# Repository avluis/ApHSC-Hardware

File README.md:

# ApHSC - Hardware
# Eagle CAD files for the ApHSC
  By: [Luis E Alvarado](mailto:admin@avnet.ws)
  
  [Software](https://github.com/avluis/ApHSC) | 
  [Hardware](https://github.com/avluis/ApHSC-Hardware)
  
# Purpose:
	To drive a ComfortHeat "Automotive Carbon Fiber Seat Heaters"
  	by Rostra with the stock control panel of a vehicle, in my case, a 2011 Suzuki Kizashi
  [Rostra Kit: 250-1872 - Universal Kit, Double thumb-dial Switch](http://www.rostra.com/manuals/250-1870_Form5261.pdf)

# Screenshots:

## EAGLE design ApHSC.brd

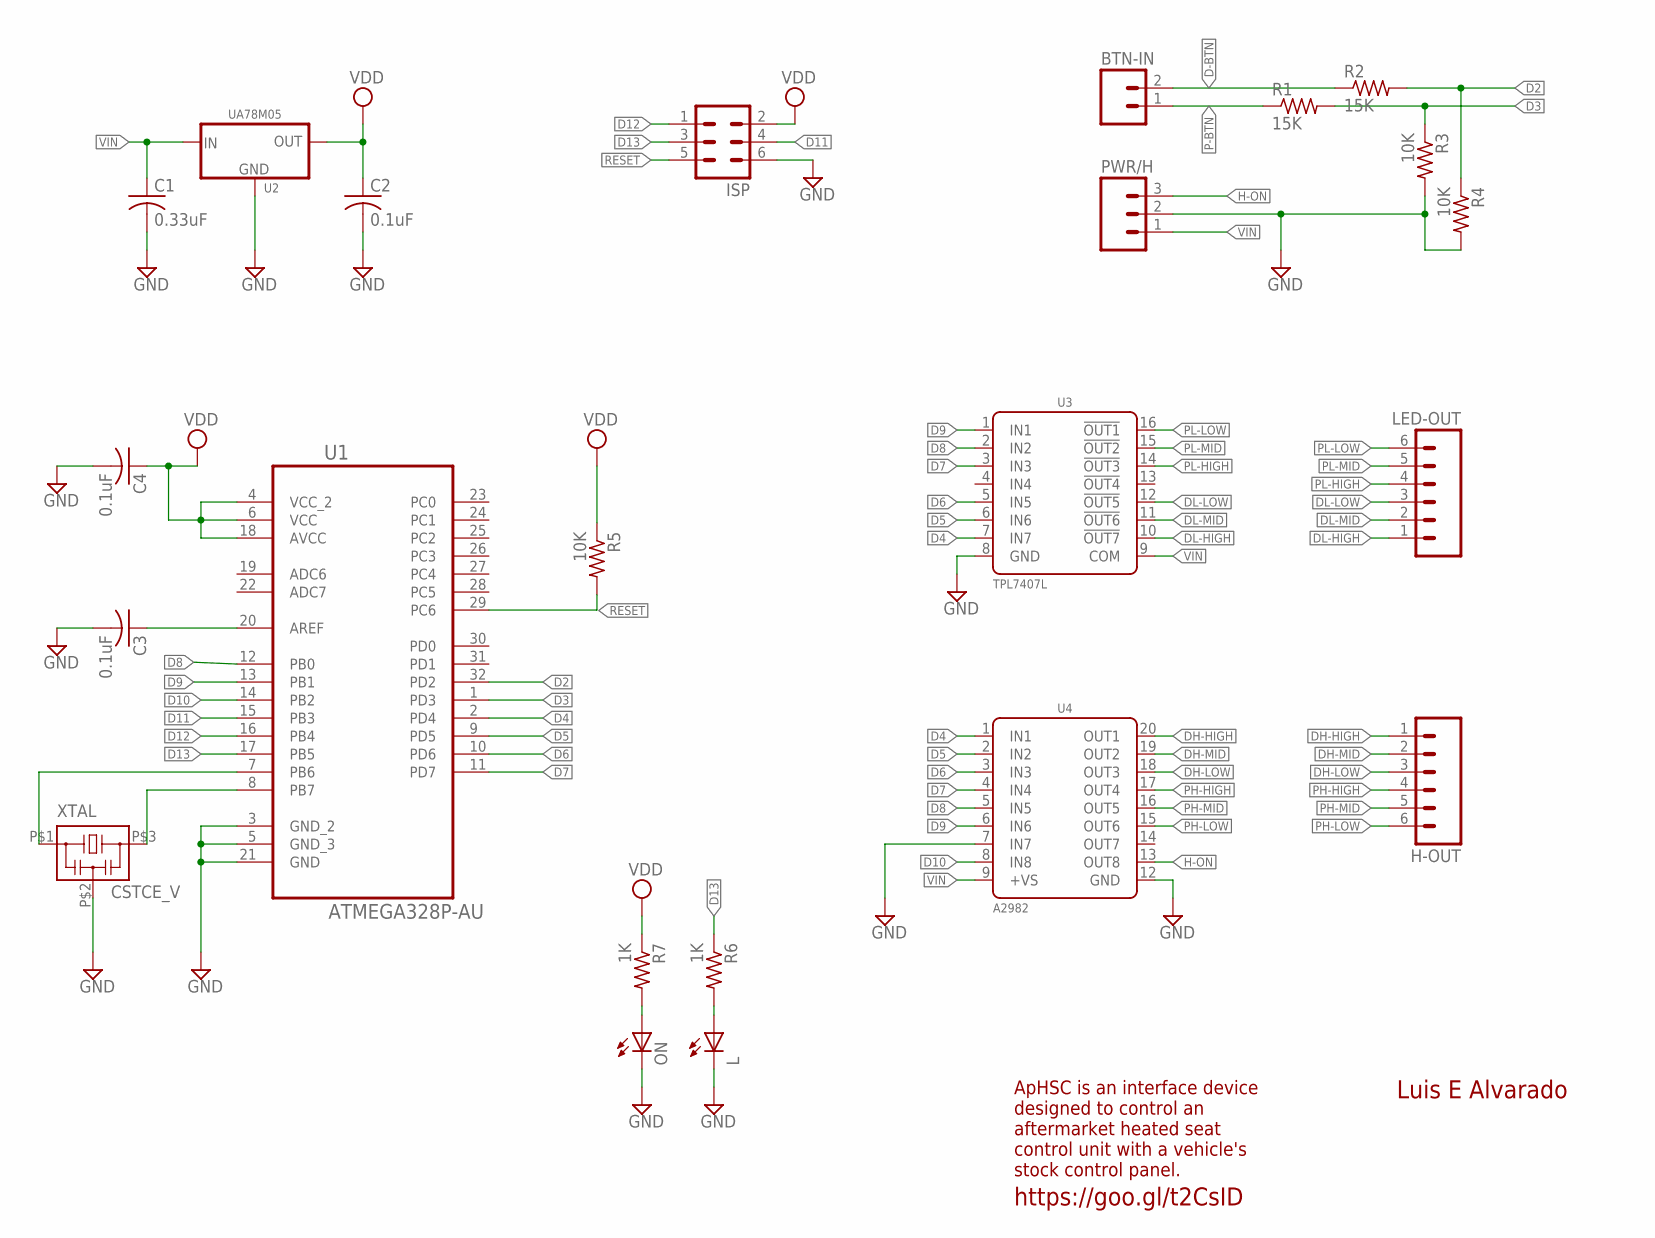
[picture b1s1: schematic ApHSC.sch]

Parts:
BTN-IN: M02PTH; 1X02
C1: 0.33uF; C0603
C2, C3, C4: 0.1uF; C0603
H-OUT: M06SIP; 1X06
ISP: MA03-2
L: LEDCHIP-LED0603; CHIP-LED0603
LED-OUT: M06SIP; 1X06
ON: LEDCHIP-LED0603; CHIP-LED0603
PWR/H: M03PTH; 1X03
R1, R2: 15K; R0603
R3, R4, R5: 10K; R0603
R6, R7: 1K; R0603
U1: ATMEGA328P-AU; QFP80P900X900X120-32N
U2: UA78M05; SOT223
U3: TPL7407L; SOIC16N
U4: A2982; SOIC20W
XTAL: CSTCE_V

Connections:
AREF: C3.1, U1.20 (AREF)
D2: R2.2, R4.1, U1.32 (PD2)
D3: R1.2, R3.1, U1.1 (PD3)
D4: U1.2 (PD4), U3.7 (IN7), U4.1 (IN1)
D5: U1.9 (PD5), U3.6 (IN6), U4.2 (IN2)
D6: U1.10 (PD6), U3.5 (IN5), U4.3 (IN3)
D7: U1.11 (PD7), U3.3 (IN3), U4.4 (IN4)
D8: U1.12 (PB0), U3.2 (IN2), U4.5 (IN5)
D9: U1.13 (PB1), U3.1 (IN1), U4.6 (IN6)
D10: U1.14 (PB2), U4.8 (IN8)
D11: ISP.4, U1.15 (PB3)
D12: ISP.1, U1.16 (PB4)
D13: ISP.3, R6.1, U1.17 (PB5)
D-BTN: BTN-IN.2, R2.1
DH-HIGH: H-OUT.1, U4.20 (OUT1)
DH-LOW: H-OUT.3, U4.18 (OUT3)
DH-MID: H-OUT.2, U4.19 (OUT2)
DL-HIGH: LED-OUT.1, U3.10 (!OUT7)
DL-LOW: LED-OUT.3, U3.12 (!OUT5)
DL-MID: LED-OUT.2, U3.11 (!OUT6)
GND: C1.2, C2.2, C3.2, C4.2, ISP.6, L.C, ON.C, PWR/H.2, R3.2, R4.2, U1.3 (GND_2), U1.5 (GND_3), U1.21 (GND), U2.2 (GND), U3.8 (GND), U4.7 (IN7), U4.12 (GND), XTAL.P$2 (2)
H-ON: PWR/H.3, U4.13 (OUT8)
unnamed: L.A, R6.2
unnamed: ON.A, R7.2
P-BTN: BTN-IN.1, R1.1
PB6: U1.7 (PB6), XTAL.P$1 (1)
PB7: U1.8 (PB7), XTAL.P$3 (3)
PH-HIGH: H-OUT.4, U4.17 (OUT4)
PH-LOW: H-OUT.6, U4.15 (OUT6)
PH-MID: H-OUT.5, U4.16 (OUT5)
PL-HIGH: LED-OUT.4, U3.14 (!OUT3)
PL-LOW: LED-OUT.6, U3.16 (!OUT1)
PL-MID: LED-OUT.5, U3.15 (!OUT2)
RESET: ISP.5, R5.2, U1.29 (PC6)
VDD: C2.1, C4.1, ISP.2, R5.1, R7.1, U1.4 (VCC_2), U1.6 (VCC), U1.18 (AVCC), U2.3 (OUT)
VIN: C1.1, PWR/H.1, U2.1 (IN), U3.9 (COM), U4.9 (+VS)

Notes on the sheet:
Luis E Alvarado
ApHSC is an interface device designed to control an aftermarket heated seat control unit with a vehicle's stock control panel.
https://goo.gl/t2CsID

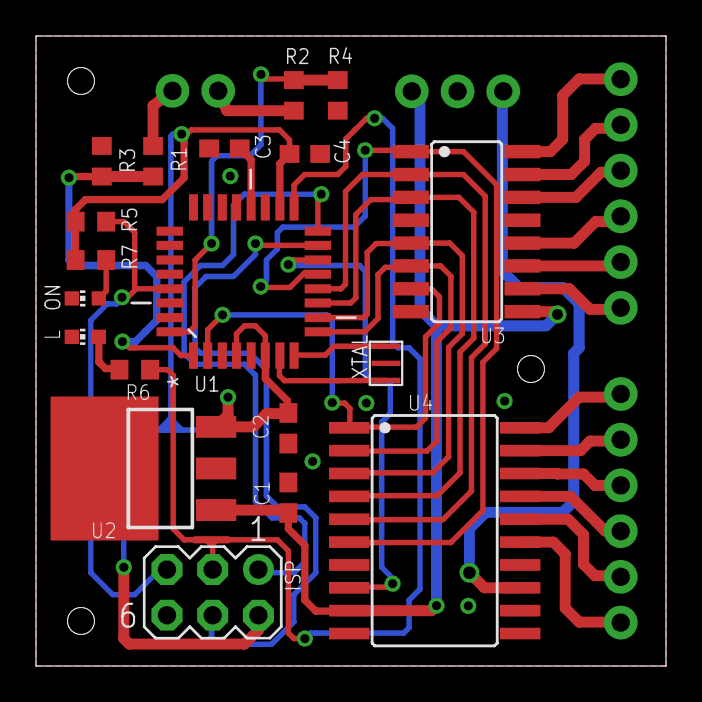
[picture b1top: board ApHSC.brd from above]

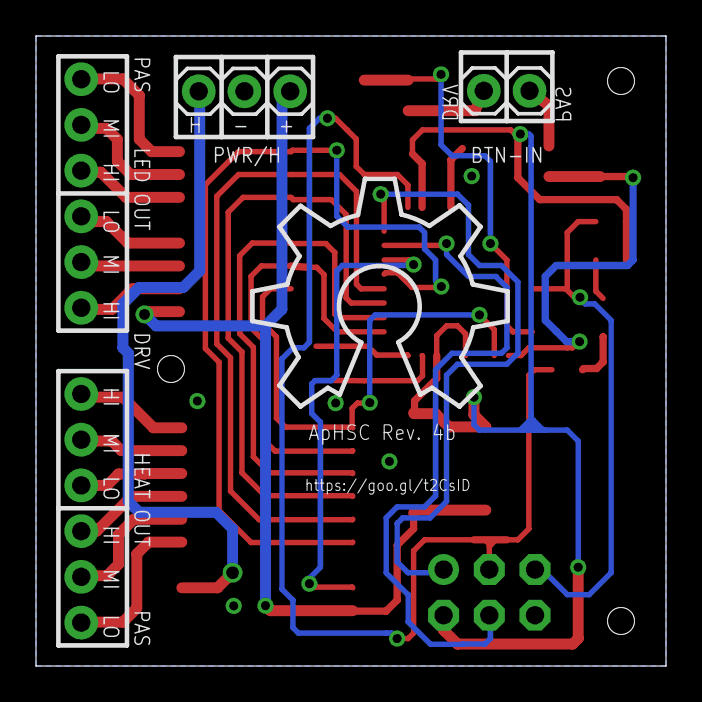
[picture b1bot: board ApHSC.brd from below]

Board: 2 copper layers, 35.0 x 35.0 mm, 24 parts (5 on the bottom side), 36 nets.

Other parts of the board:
U$1: OSHW_10X500_NOTEXT

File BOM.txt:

Partlist exported from /Users/avluis/git/ArduinoHeatedSeatController-Hardware/Arduino_Heated_Seats_Controller.sch at 8/12/15 17:07

Part    Value         Device          Package               Description                                             
BTN-IN                M02PTH          1X02                  Standard 2-pin 0.1" header. Use with                    
C1      0.33uF        C-USC0603       C0603                 CAPACITOR, American symbol                              
C2      0.1uF         C-USC0603       C0603                 CAPACITOR, American symbol                              
C3      0.1uF         C-USC0603       C0603                 CAPACITOR, American symbol                              
C4      0.1uF         C-USC0603       C0603                 CAPACITOR, American symbol                              
H-OUT                 M06SIP          1X06                  Header 6                                                
ISP                   MA03-2          MA03-2                PIN HEADER                                              
L                     LEDCHIP-LED0603 CHIP-LED0603          LED                                                     
LED-OUT               M06SIP          1X06                  Header 6                                                
ON                    LEDCHIP-LED0603 CHIP-LED0603          LED                                                     
PWR/H                 M03PTH          1X03                  Header 3                                                
R1      15K           R-US_R0603      R0603                 RESISTOR, American symbol                               
R2      15K           R-US_R0603      R0603                 RESISTOR, American symbol                               
R3      10K           R-US_R0603      R0603                 RESISTOR, American symbol                               
R4      10K           R-US_R0603      R0603                 RESISTOR, American symbol                               
R5      10K           R-US_R0603      R0603                 RESISTOR, American symbol                               
R6      1K            R-US_R0603      R0603                 RESISTOR, American symbol                               
R7      1K            R-US_R0603      R0603                 RESISTOR, American symbol                               
U1      ATMEGA328P-AU ATMEGA328P-AU   QFP80P900X900X120-32N 8-bit Microcontroller with In-System Programmable Flash 
U2      UA78M05       UA78M05         SOT223                μA78Mxx Positive-Voltage Regulators                     
U3      TPL7407L      TPL7407L        SOIC16N               40V 7-Channel Low Side Driver                           
U4      A2982         A2982           SOIC20W               8-Channel Source Driver                                 
XTAL    CSTCE_V       CSTCE_V         CSTCE_V

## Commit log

2015-02-08 ignore eagle pref file
2015-02-08 Common Arduino library
2015-02-08 M54564P-FP Custom library http://datasheet.eeworld.com.cn/pdf/MITSUBISHI/45556_M54564FP.pdf
2015-02-08 Schematic & Board - rev 2 https://oshpark.com/shared_projects/5AbDykNL
2015-02-08 Basic parts list Will be updating later with proper links to individual parts.
2015-02-08 Revision 2 schematic pdf
2015-03-28 More to read (and type).
2015-04-03 Updated.
2015-04-03 Added global .gitignore file.
2015-04-29 Removed needlessly long part description - format whitespace.
2015-04-29 Added release link.
2015-04-29 Release comment.
2015-04-29 I love tweaking .md files.
2015-04-29 Initial work on rev3 underway (time for some sleep).
2015-04-30 ULN2003A replaced with ULN2803A (both from Texas Instruments - but with one more input, cheaper and actually available without jumping to eBay). Work on replacing the M54564P underway.
2015-04-30 Revert "ULN2003A replaced with ULN2803A (both from Texas Instruments - but with one more input, cheaper and actually available without jumping to eBay)."
    This reverts commit adf95428dccab3bb593bcfff33bcf90c1b5228b2.
2015-04-30 Settled for an ULN2003A (compatible with Toshiba variant) and the TD62783AFG (from Toshiba as well).
2015-04-30 Additional pads for TX and RX (if needed).
2015-04-30 Initial layout & routing complete - started work on silk layer (traces: need to tweak width on certain traces to handle load current).
2015-04-30 Swapped MIC5219B for uA78M05I to handle higher input voltage (and lower operating environment temps). Swapped a few capacitors (removed polarized 0.1uF on regulator output). Removed a few pads not ne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
2015-05-01 A few more layout changes to accommodate part changes and physical part dimensions. Still a few more things to add (drills for mounting, traces to widen, silk to add) but nothing major.
2015-05-02 Added reset label to trace on reset pin.
2015-05-02 More tweaks to traces (hopefully final). More silk labels (on pins as well). Holes (for mounting). And anything else I might have forgotten - looks ready to send to fab for electrical test.
2015-06-08 Bill of Materials - prepping for a v4 - reverting to a single sided for easier solder/reflow.
2015-06-08 Changes: Removed test pins.
    Corrections:
    Removed ground on ULN2003A pin 9.
    GND on ULN2003A is pin 8 (pin 9 is COMMON/E).
2015-06-09 Changes so far - commit before tweaking trace width and misc.
2015-06-10 Final tweaks and changes - off to the fab house.
2015-06-10 Oops, drill in the wrong location - fixed - v4 is ready for OSH Park (for real this time). Plans for v5 in the works - simply to replace v3. v4 and v5 will be interchangeable (only difference will be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
2015-06-10 ERC check.
2015-06-10 Additional silkscreen and trace width tweaks before sending to OSH Park (still v4).
2015-06-10 Small position tweak to allow ground pour around connectors.
2015-08-03 Added rev4 screenshots.
2015-08-03 Attempting to add screenshots to README.
2015-08-03 Failing at adding screenshots.
2015-08-03 Moving screenshots to top level folder (in branch).
2015-08-03 Revision 4 release.
2015-08-03 Access rev2 from Releases or commit history.
2015-08-03 Removing releases link (while searching for a M54564P/FP replacement).
2015-08-03 Library error - need to make sure the rest of my libraries are correct are well.
2015-08-03 More patching.
2015-08-03 Grounding unused input pins (compatibility with A2982SLWTR-T). Tweak routing and vias.
2015-08-04 Swapped ATMega from unknown library with Element14 library. Moved silkscreen (web address) to other side of board.
2015-08-05 Enough changes to warrant a minor revision bump. Equivalent parts have been selected for testing - will need to update design if tests are good. Current design should be compatible with selected part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
2015-08-12 Changes from freelancer.com - lovely~
2015-08-12 Tweaking silkscreen.
2015-08-12 Files received back from freelancer.com (before my tweaks and merge).
2015-08-12 Tweaking a few things.
2015-08-14 Updated project name & links.
2015-08-14 Renamed files.
2015-08-14 Minor stylistic edits.
2015-08-14 BOM text file replaced for excel sheet. BOM complete with Digi-Key part numbers.
2015-08-14 Using SketchUp and eagleUp to build a 3D model.
2015-08-14 Small layout changes - tweaked position of vias and silkscreen.
2015-08-14 More silkscreen tweaks. Moved Heat/LED silkscreen to bottom layer.

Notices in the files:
parts and their libraries:
SparkFun-Connectors: Licensing: Creative Commons ShareAlike 4.0 International - https://creativecommons.org/licenses/by-sa/4.0
